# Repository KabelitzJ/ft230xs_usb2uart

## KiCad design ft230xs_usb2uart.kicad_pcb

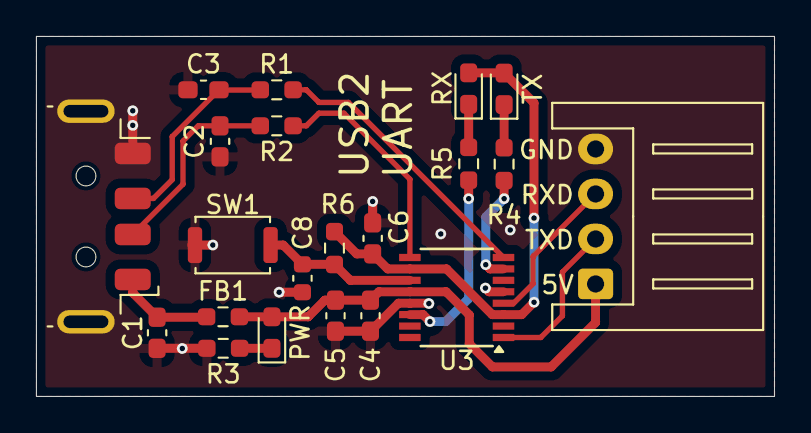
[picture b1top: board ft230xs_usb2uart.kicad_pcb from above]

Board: 2 copper layers, 41.0 x 20.0 mm, 21 parts (0 on the bottom side), 12 nets.

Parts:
C1: 10n; C_0603_1608Metric_Pad1.08x0.95mm_HandSolder
C2, C3: 47p; C_0603_1608Metric_Pad1.08x0.95mm_HandSolder
C4, C6: 100n; C_0603_1608Metric_Pad1.08x0.95mm_HandSolder
C5: 4u7; C_0603_1608Metric_Pad1.08x0.95mm_HandSolder
C8: 100n; C_0603_1608Metric
FB1: FerriteBead; R_0603_1608Metric_Pad0.98x0.95mm_HandSolder
J1: USB_A; USB_A_Molex_48037-2200_Horizontal
J2: Conn_01x04_Socket; JST_XH_S4B-XH-A_1x04_P2.50mm_Horizontal
PWR: LED; LED_0603_1608Metric_Pad1.05x0.95mm_HandSolder
R1, R2: 27; R_0603_1608Metric_Pad0.98x0.95mm_HandSolder
R3, R4, R5: 270; R_0603_1608Metric_Pad0.98x0.95mm_HandSolder
R6: 10k; R_0603_1608Metric_Pad0.98x0.95mm_HandSolder
RX: LED; LED_0603_1608Metric_Pad1.05x0.95mm_HandSolder
SW1: SW_Push; SW_Push_SPST_NO_Alps_SKRK
TX: LED; LED_0603_1608Metric_Pad1.05x0.95mm_HandSolder
U3: FT230XS; SSOP-16_3.9x4.9mm_P0.635mm

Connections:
+3V3: C6.1, R6.2, RX.2 (A), TX.2 (A), U3.3 (VCCIO), U3.10 (3V3OUT)
+5V: C4.1, C5.1, FB1.2, J2.1, PWR.2 (A), U3.12 (VCC)
/PWR_LED: PWR.1 (K), R3.2
GND: C1.2, C2.2, C3.2, C4.2, C5.2, C6.2, C8.2, J1.4 (GND), J1.5 (Shield), J2.4, R3.1, SW1.1, U3.5 (GND), U3.13 (GND)
RXD: J2.3, U3.4 (RXD)
RX_LED: R5.1, R5.2, RX.1 (K), U3.14 (CBUS1)
TXD: J2.2, U3.1 (TXD)
TX_LED: R4.1, R4.2, TX.1 (K), U3.7 (CBUS2)
USB_D+: C3.1, J1.3 (D+), R1.1, R1.2, U3.8 (USBDP)
USB_D-: C2.1, J1.2 (D-), R2.1, R2.2, U3.9 (USBDM)
VBUS: C1.1, FB1.1, J1.1 (VBUS)
~RST: C8.1, R6.1, SW1.2, U3.11 (~RESET)

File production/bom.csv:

Designator,Footprint,Quantity,Value,LCSC Part #
C1,0603,1,10n,
"C2, C3",0603,2,47p,
"C4, C6, C8",0603,3,100n,
C5,0603,1,4u7,
FB1,0603,1,FerriteBead,
J1,USB_A_Molex_48037-2200_Horizontal,1,USB_A,
J2,JST_XH_S4B-XH-A_1x04_P2.50mm_Horizontal,1,Conn_01x04_Socket,
"PWR, RX, TX",0603,3,LED,
"R1, R2",0603,2,27,
"R3, R4, R5",0603,3,270,
R6,0603,1,10k,
SW1,SW_Push_SPST_NO_Alps_SKRK,1,SW_Push,
U3,SSOP-16_3.9x4.9mm_P0.635mm,1,FT230XS,

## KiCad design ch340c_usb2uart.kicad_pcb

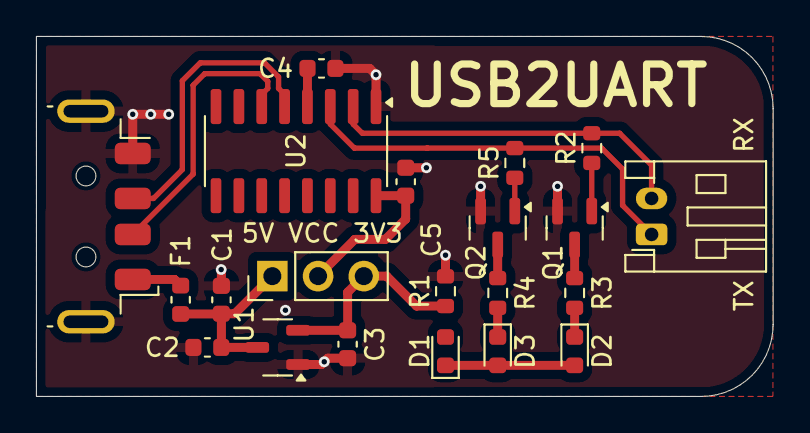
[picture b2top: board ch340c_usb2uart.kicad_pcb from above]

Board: 2 copper layers, 40.9 x 20.0 mm, 21 parts (0 on the bottom side), 10 nets.

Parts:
C1: 4u7; C_0603_1608Metric
C2, C3: 1u; C_0603_1608Metric
C4, C5: 100n; C_0603_1608Metric
D1: PWR; LED_0603_1608Metric
D2: TX (Orange); LED_0603_1608Metric
D3: RX (Green); LED_0603_1608Metric
F1: Polyfuse; Fuse_0603_1608Metric
J1: USB_A; USB_A_Molex_48037-2200_Horizontal
J2: Conn_01x02_Socket; JST_PH_S2B-PH-K_1x02_P2.00mm_Horizontal
J3: Conn_01x03_Pin; PinHeader_1x03_P2.54mm_Vertical
Q1, Q2: BC856; SOT-23
R1, R3, R4: 330; R_0603_1608Metric
R2, R5: 4k7; R_0603_1608Metric
U1: MCP1700x-330xxTT; SOT-23-3
U2: CH340C; SOIC-16_3.9x9.9mm_P1.27mm

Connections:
+3V3: C3.1, D1.1 (K), D1.2 (A), D2.1 (K), D2.2 (A), D3.1 (K), D3.2 (A), J3.3, Q1.3 (C), Q2.3 (C), R1.1, R3.1, R3.2, R4.1, R4.2, U1.2 (VO)
+5V: C1.1, C2.1, F1.2, J3.1, U1.3 (VI)
GND: C1.2, C2.2, C3.2, C4.2, C5.2, J1.4 (GND), J1.5 (Shield), Q1.2 (E), Q2.2 (E), R1.2, U1.1 (GND), U2.1 (GND)
RX: J2.1, Q2.1 (B), R5.1, R5.2, U2.3 (RXD)
TX: J2.2, Q1.1 (B), R2.1, R2.2, U2.2 (TXD)
USB_D+: J1.3 (D+), U2.5 (UD+)
USB_D-: J1.2 (D-), U2.6 (UD-)
V3: C4.1, U2.4 (V3)
VBUS: F1.1, J1.1 (VBUS)
VCC: C5.1, J3.2, U2.16 (VCC)

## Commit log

2025-03-19 init
2025-03-19 asdasd
2025-03-19 adasd
